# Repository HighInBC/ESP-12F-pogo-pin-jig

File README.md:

# ESP-12F-pogo-pin-jig
A jig to connect up to a ESP-12F using pogo pins

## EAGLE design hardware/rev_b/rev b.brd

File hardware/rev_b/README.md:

Recieved from fab, but not yet tested.

Not even close to fitting. I think I will get it right next time. Do not use.

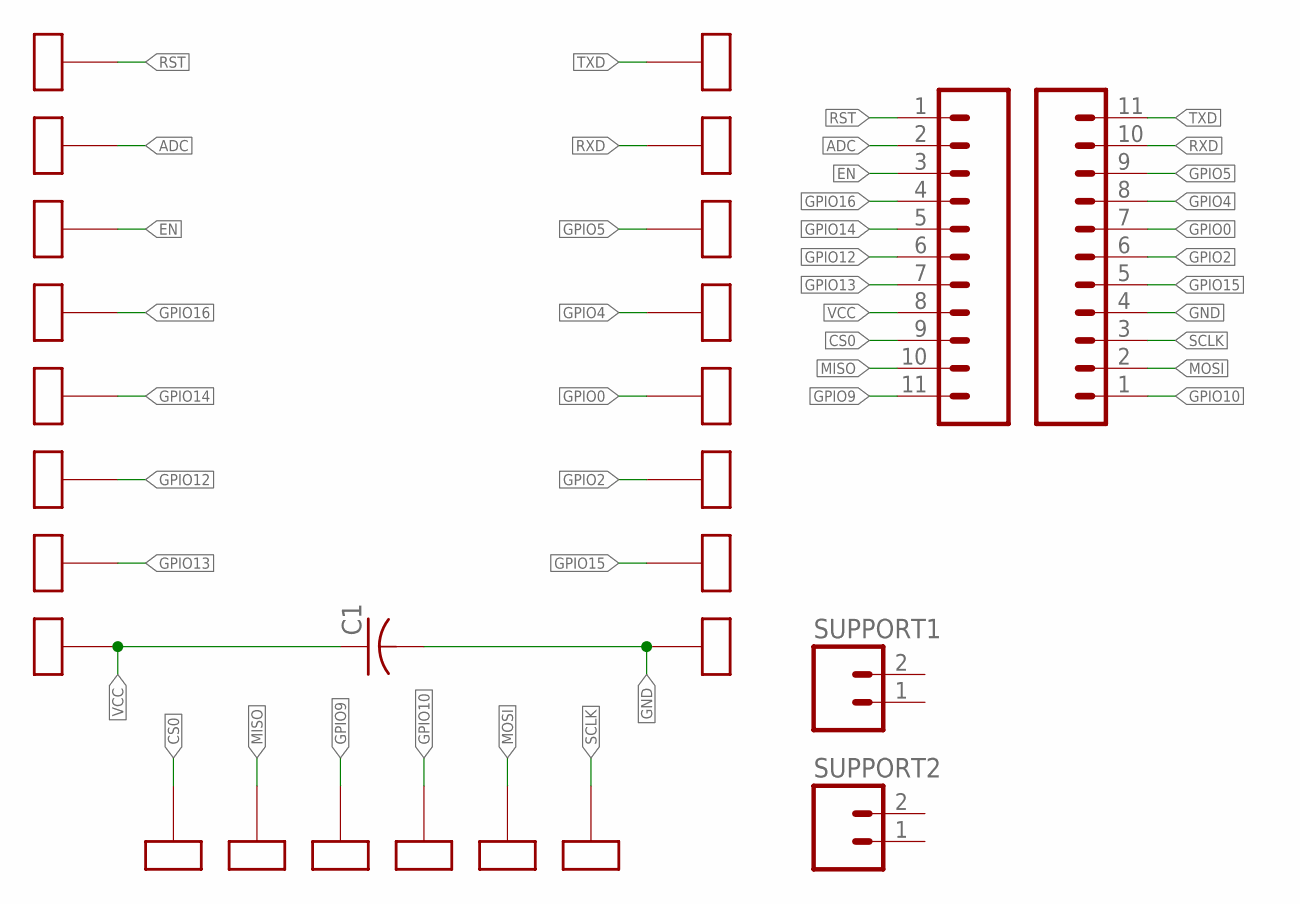
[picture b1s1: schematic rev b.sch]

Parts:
C1: C-USC0805; C0805
JP1, JP2: M11LOCK; 1X11_LOCK
SUPPORT1, SUPPORT2: M02LOCK; 1X02_LOCK
U$2, U$3, U$4, U$5, U$6, U$7, U$8, U$9, U$10, U$11, U$12, U$13, U$14, U$15, U$16, U$17, U$18, U$19, U$20, U$21, U$22, U$23: 1MMPOGO

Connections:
ADC: JP1.2, U$3.POGO
CS0: JP1.9, U$10.POGO
EN: JP1.3, U$4.POGO
GND: C1.2, JP2.4, U$16.POGO
GPIO0: JP2.7, U$19.POGO
GPIO2: JP2.6, U$18.POGO
GPIO4: JP2.8, U$20.POGO
GPIO5: JP2.9, U$21.POGO
GPIO9: JP1.11, U$12.POGO
GPIO10: JP2.1, U$13.POGO
GPIO12: JP1.6, U$7.POGO
GPIO13: JP1.7, U$8.POGO
GPIO14: JP1.5, U$6.POGO
GPIO15: JP2.5, U$17.POGO
GPIO16: JP1.4, U$5.POGO
MISO: JP1.10, U$11.POGO
MOSI: JP2.2, U$14.POGO
RST: JP1.1, U$2.POGO
RXD: JP2.10, U$22.POGO
SCLK: JP2.3, U$15.POGO
TXD: JP2.11, U$23.POGO
VCC: C1.1, JP1.8, U$9.POGO

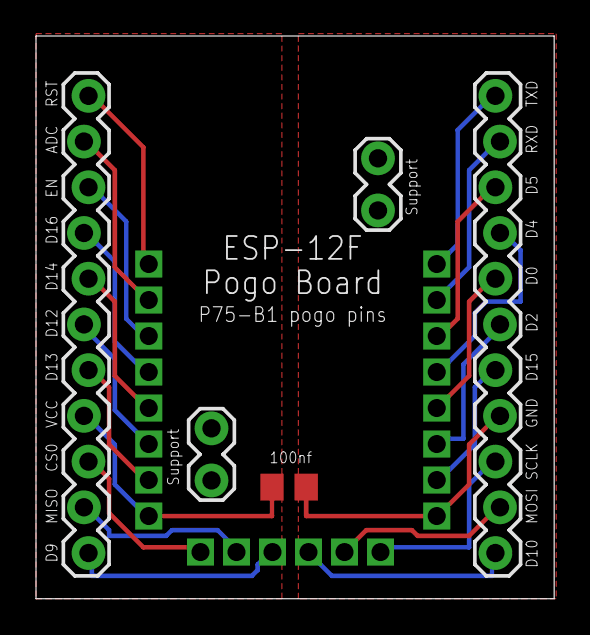
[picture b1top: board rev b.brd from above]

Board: 2 copper layers, 28.8 x 31.3 mm, 27 parts (0 on the bottom side), 22 nets.

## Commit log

2016-08-01 Adding initial attempt
2016-08-01 adding readme
2016-08-01 rearrange
2016-08-05 licsense
2016-08-12 update info

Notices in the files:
parts and their libraries:
SparkFun-Connectors: Licensing: Creative Commons ShareAlike 4.0 International - https://creativecommons.org/licenses/by-sa/4.0
